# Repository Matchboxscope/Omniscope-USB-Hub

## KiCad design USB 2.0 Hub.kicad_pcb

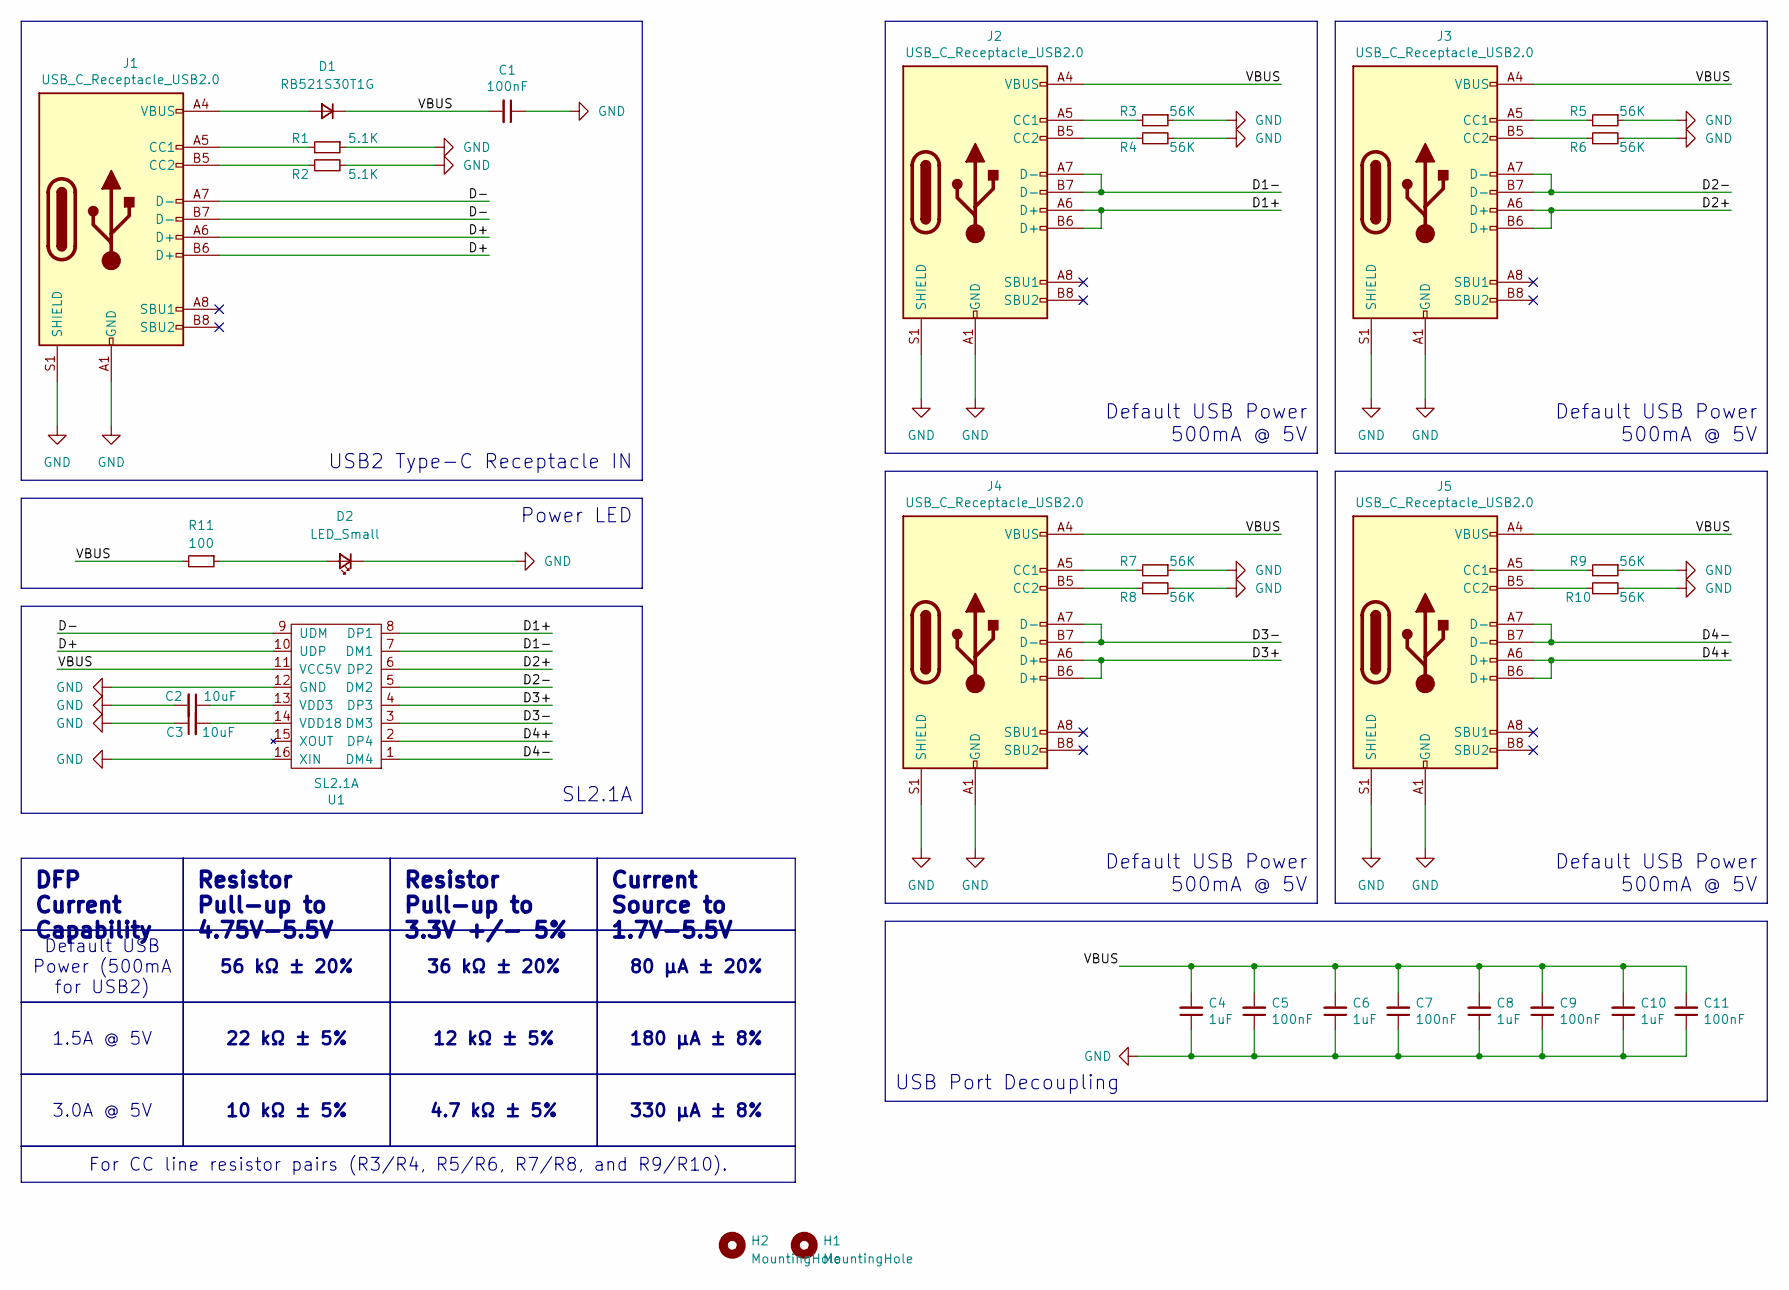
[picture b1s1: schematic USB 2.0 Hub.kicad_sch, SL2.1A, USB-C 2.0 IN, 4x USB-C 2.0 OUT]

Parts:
C1, C5, C7, C9, C11: 100nF; C_0805_2012Metric_Pad1.18x1.45mm_HandSolder
C2, C3: 10uF; C_0805_2012Metric_Pad1.18x1.45mm_HandSolder
C4, C6, C8, C10: 1uF; C_0805_2012Metric_Pad1.18x1.45mm_HandSolder
D1: RB521S30T1G; D_SOD-523
D2: LED_Small; LED_1206_3216Metric_Pad1.42x1.75mm_HandSolder
H1, H2: MountingHole; MountingHole_3.2mm_M3_ISO14580
J1: USB_C_Receptacle_USB2.0; USB_C_Receptacle_HRO_TYPE-C-31-M-12
J2, J3, J4, J5: USB_C_Receptacle_USB2.0; USB_C_Receptacle_U261-241N-4BS2SS
R1, R2: 5.1K; R_0805_2012Metric_Pad1.20x1.40mm_HandSolder
R3, R4, R5, R6, R7, R8, R9, R10: 56K; R_0805_2012Metric_Pad1.20x1.40mm_HandSolder
R11: 100; R_0805_2012Metric_Pad1.20x1.40mm_HandSolder
U1: SL2.1A; SOIC-16_4.55x10.3mm_P1.27mm

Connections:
/D1+: J2.A6 (D+), J2.B6 (D+), U1.8 (DP1)
/D1-: J2.A7 (D-), J2.B7 (D-), U1.7 (DM1)
/D2+: J3.A6 (D+), J3.B6 (D+), U1.6 (DP2)
/D2-: J3.A7 (D-), J3.B7 (D-), U1.5 (DM2)
/D3+: J4.A6 (D+), J4.B6 (D+), U1.4 (DP3)
/D3-: J4.A7 (D-), J4.B7 (D-), U1.3 (DM3)
/D4+: J5.A6 (D+), J5.B6 (D+), U1.2 (DP4)
/D4-: J5.A7 (D-), J5.B7 (D-), U1.1 (DM4)
/D+: J1.A6 (D+), J1.B6 (D+), U1.10 (UDP)
/D-: J1.A7 (D-), J1.B7 (D-), U1.9 (UDM)
/VBUS: C1.2, C4.2, C5.2, C6.2, C7.2, C8.2, C9.2, C10.2, C11.2, D1.1 (K), J2.A4 (VBUS), J2.A9 (VBUS), J2.B4 (VBUS), J2.B9 (VBUS), J3.A4 (VBUS), J3.A9 (VBUS), J3.B4 (VBUS), J3.B9 (VBUS), J4.A4 (VBUS), J4.A9 (VBUS), J4.B4 (VBUS), J4.B9 (VBUS), J5.A4 (VBUS), J5.A9 (VBUS), J5.B4 (VBUS), J5.B9 (VBUS), R11.2, U1.11 (VCC5V)
GND: C1.1, C2.2, C3.1, C4.1, C5.1, C6.1, C7.1, C8.1, C9.1, C10.1, C11.1, D2.1 (K), J1.A1 (GND), J1.A12 (GND), J1.B1 (GND), J1.B12 (GND), J1.S1 (SHIELD), J2.A1 (GND), J2.A12 (GND), J2.B1 (GND), J2.B12 (GND), J2.S1 (SHIELD), J3.A1 (GND), J3.A12 (GND), J3.B1 (GND), J3.B12 (GND), J3.S1 (SHIELD), J4.A1 (GND), J4.A12 (GND), J4.B1 (GND), J4.B12 (GND), J4.S1 (SHIELD), J5.A1 (GND), J5.A12 (GND), J5.B1 (GND), J5.B12 (GND), J5.S1 (SHIELD), R1.1, R2.2, R3.1, R4.2, R5.1, R6.2, R7.1, R8.2, R9.1, R10.2, U1.12 (GND), U1.16 (XIN)
unnamed: D1.2 (A), J1.A4 (VBUS), J1.A9 (VBUS), J1.B4 (VBUS), J1.B9 (VBUS)
unnamed: D2.2 (A), R11.1
unnamed: J1.A5 (CC1), R1.2
unnamed: J1.B5 (CC2), R2.1
unnamed: J2.A5 (CC1), R3.2
unnamed: J2.B5 (CC2), R4.1
unnamed: J3.A5 (CC1), R5.2
unnamed: J3.B5 (CC2), R6.1
unnamed: J4.A5 (CC1), R7.2
unnamed: J4.B5 (CC2), R8.1
unnamed: J5.A5 (CC1), R9.2
unnamed: J5.B5 (CC2), R10.1
unnamed: C2.1, U1.13 (VDD3)
unnamed: C3.2, U1.14 (VDD18)

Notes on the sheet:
Resistor Pull-up to 4.75V-5.5V
For CC line resistor pairs (R3/R4, R5/R6, R7/R8, and R9/R10).
22 kΩ ± 5%
12 kΩ ± 5%
330 μA ± 8%
Current Source to 1.7V-5.5V
4.7 kΩ ± 5%
36 kΩ ± 20%
DFP Current Capability
56 kΩ ± 20%
80 μA ± 20%
Resistor Pull-up to 3.3V +/- 5%
180 μA ± 8%
1.5A @ 5V
10 kΩ ± 5%
3.0A @ 5V
Default USB Power (500mA for USB2)
SL2.1A
Default USB Power 500mA @ 5V
USB2 Type-C Receptacle IN
USB Port Decoupling
Power LED

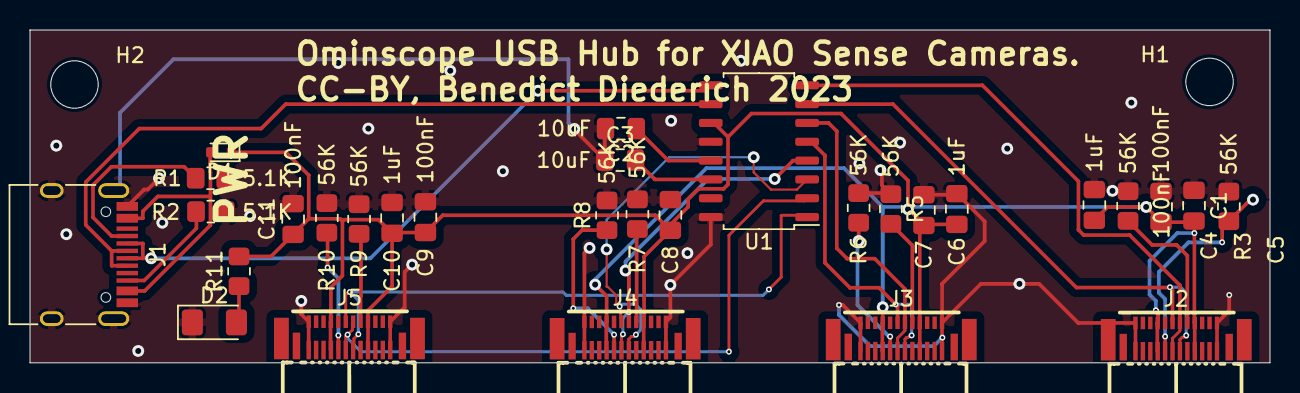
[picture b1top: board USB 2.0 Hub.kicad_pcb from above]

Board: 2 copper layers, 83.7 x 22.5 mm, 32 parts (0 on the bottom side), 26 nets.

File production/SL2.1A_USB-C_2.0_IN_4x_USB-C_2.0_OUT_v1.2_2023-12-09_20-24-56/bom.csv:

Designator,Footprint,Quantity,Value,LCSC Part #
"C1, C11, C5, C7, C9",0805,5,100nF,
"C10, C4, C6, C8",0805,4,1uF,
"C2, C3",0805,2,10uF,
D1,1206,1,SD1206T020S1R0,
D2,1206,1,LED_Small,
"H1, H2",MountingHole_3.2mm_M3_ISO14580,2,MountingHole,
J1,USB_C_Receptacle_HRO_TYPE-C-31-M-12,1,USB_C_Receptacle_USB2.0,
"J2, J3, J4, J5",USB_C_Plug_UTC009-C12,4,USB_C_Receptacle_USB2.0,
"R1, R2",0805,2,5.1K,
"R10, R3, R4, R5, R6, R7, R8, R9",0805,8,56K,
R11,0805,1,100,
U1,SOIC-16_4.55x10.3mm_P1.27mm,1,SL2.1A,

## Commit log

2023-12-06 Adjusting size to match wellplate
2023-12-08 update gitignore
2023-12-08 Fixed pending connections
2023-12-10 Swapping USB connectors
2023-12-10 updating outline

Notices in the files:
USB 2.0 Hub.kicad_pcb:
CC-BY, Benedict Diederich 2023
